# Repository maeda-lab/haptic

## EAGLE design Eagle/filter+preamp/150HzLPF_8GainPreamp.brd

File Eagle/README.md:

Eagle 9.4.1 Education Miyamoto2019/6/6

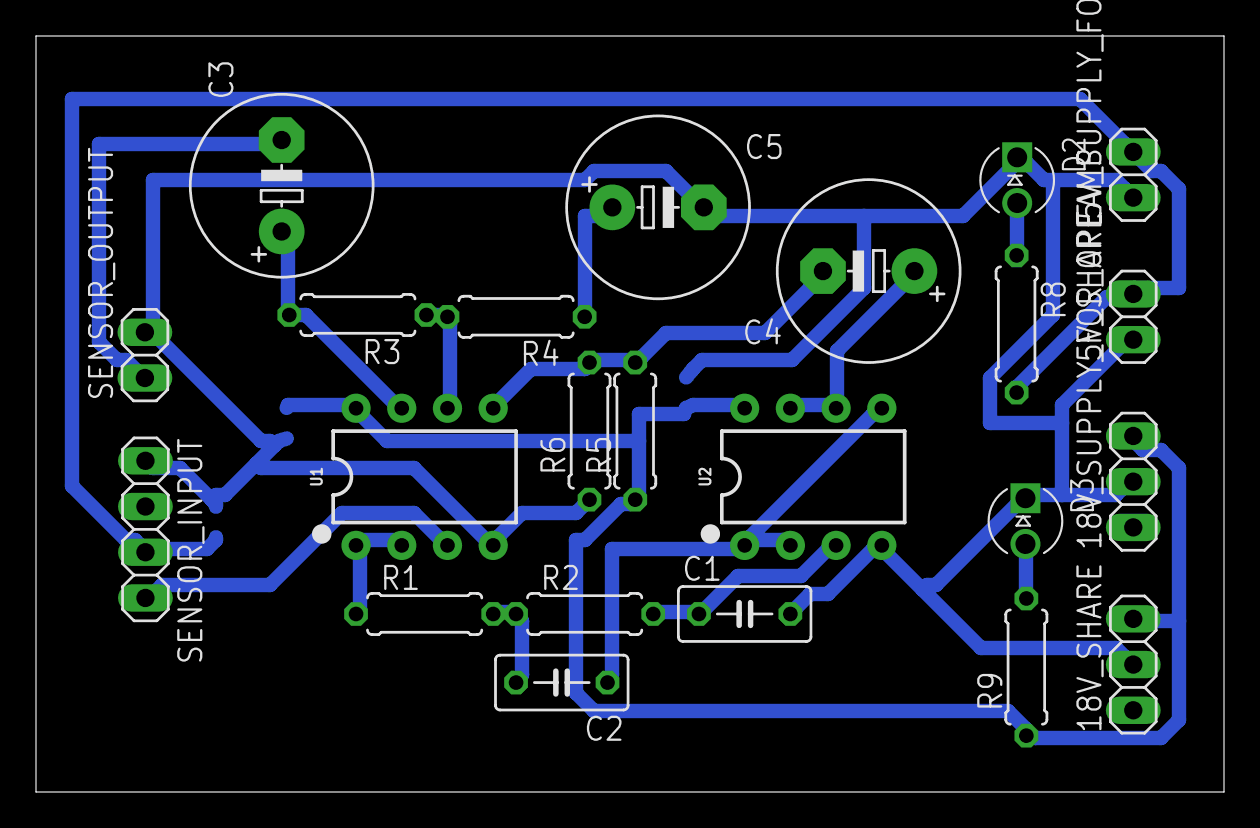
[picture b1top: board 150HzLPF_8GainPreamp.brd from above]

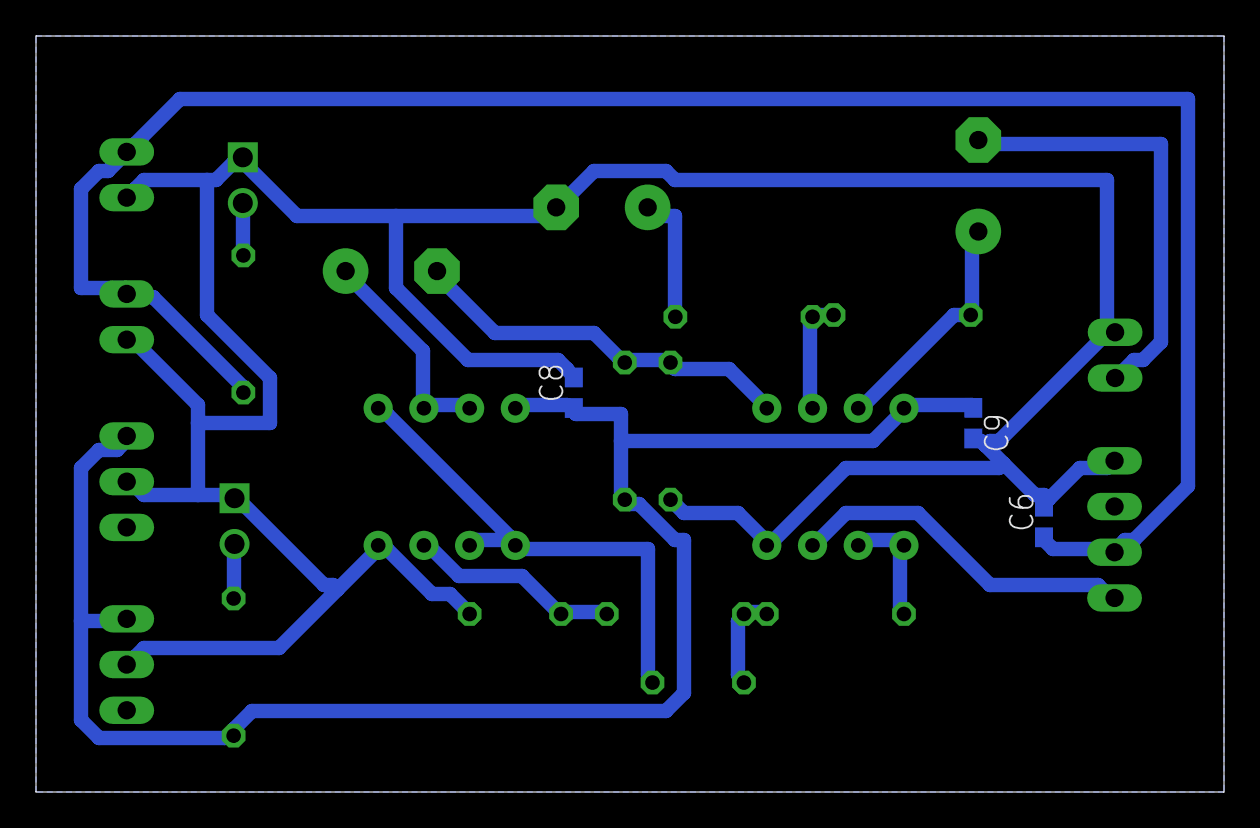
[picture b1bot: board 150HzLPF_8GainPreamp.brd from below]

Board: 2 copper layers, 66.0 x 42.0 mm, 26 parts (3 on the bottom side), 16 nets.

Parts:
5V_SHARE, 5V_SUPPLY_FOR_SENSOR: 1X02
18V_SHARE, 18V_SUPPLY_FOR_OPEAMP: 1X03
C1, C2: 0.1u; C050-030X075
C3: 150u; E5-10,5
C4, C5: 1u or 2.2u; E5-10,5
C6: 0.1u; C0603
C8, C9: 33u; C0603
D2, D3: LTL-1CHE; RADIAL_3MM
R1, R2, R4, R5, R6: 10k; 0207/7
R3: 180k; 0207/7
R8: 760; 0207/7
R9: 3.3k; 0207/7
SENSOR_INPUT: 1X04
SENSOR_OUTPUT: 1X02
U1, U2: LM358; DIP08

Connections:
5V_VCC: 5V_SHARE.2, 5V_SUPPLY_FOR_SENSOR.2, C6.1, R8.2, SENSOR_INPUT.3
18V_VCC: 18V_SHARE.3, 18V_SUPPLY_FOR_OPEAMP.3, C8.1, C9.1, R5.1, R9.1, U1.8, U2.8
GND: 5V_SHARE.1, 5V_SUPPLY_FOR_SENSOR.1, 18V_SHARE.2, 18V_SUPPLY_FOR_OPEAMP.2, C1.2, C5.-, C6.2, C8.2, C9.2, D2.C, D3.C, R6.1, SENSOR_INPUT.1, SENSOR_OUTPUT.2, U1.4, U2.4
unnamed: R1.1, U1.1, U1.2
unnamed: C2.2, R1.2, R2.1
unnamed: C1.1, R2.2, U2.3
unnamed: C2.1, U2.1, U2.2, U2.5
unnamed: SENSOR_INPUT.4, U1.3
unnamed: C4.+, U2.6, U2.7
unnamed: R3.1, R4.2, U1.6
unnamed: C3.+, R3.2, U1.7
unnamed: C4.-, R5.2, R6.2, U1.5
unnamed: C5.+, R4.1
unnamed: D2.A, R8.1
unnamed: C3.-, SENSOR_OUTPUT.1
unnamed: D3.A, R9.2

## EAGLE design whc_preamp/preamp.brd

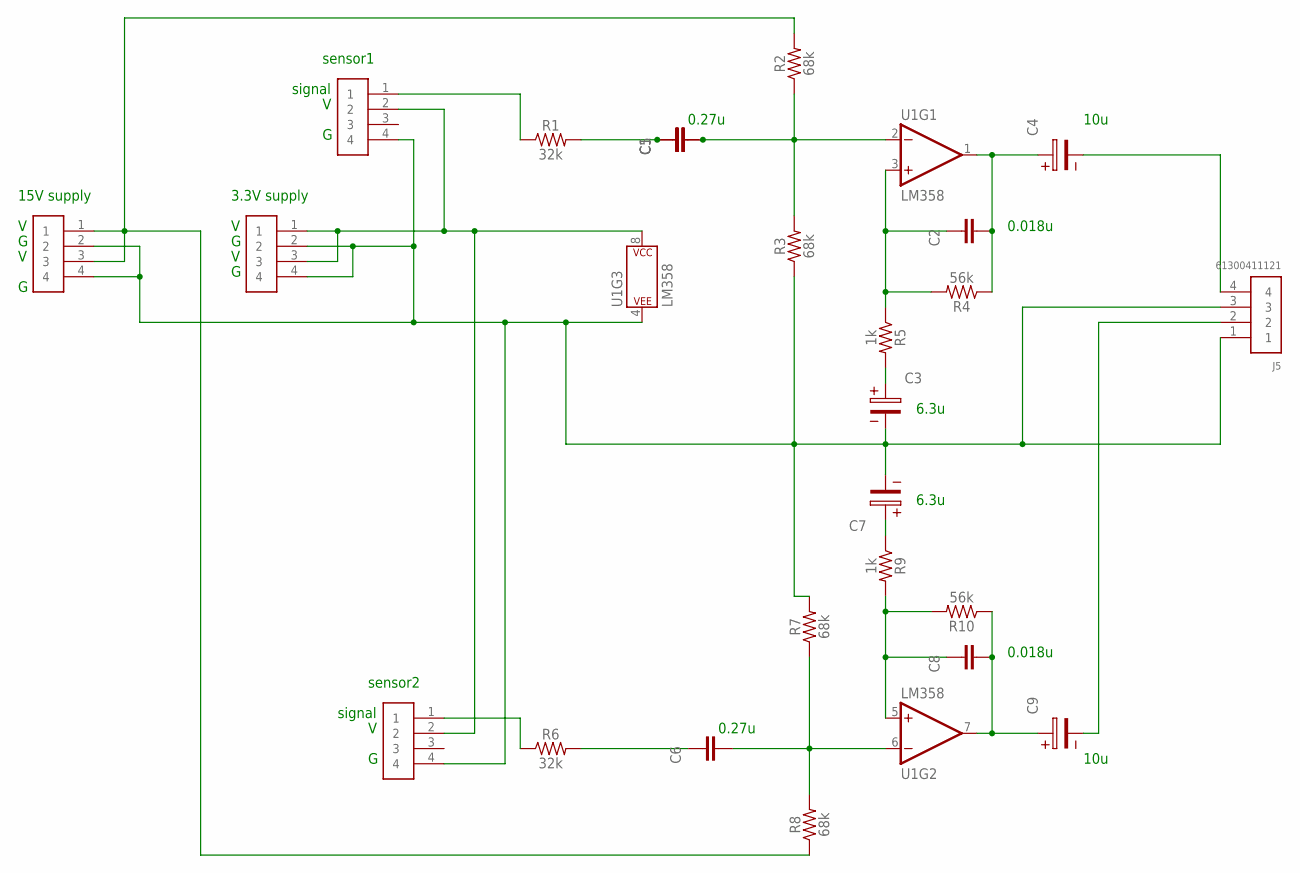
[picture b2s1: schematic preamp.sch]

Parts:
C1, C6, C8: CC0603JRNPO9BN270; CAP_0603
C2: 0.018u; CAP_0603
C3, C4, C7, C9: WCAP-AI3H_25X30_861141084008; 25X10X2(DXPXΦ)
C5: 0.27u; CAP_0603
J1, J2, J3, J4, J5: 61300411121
R1, R6: 32k; AXIAL-0.3
R2, R3, R7, R8: 68k; AXIAL-0.3
R4, R10: 56k; AXIAL-0.3
R5, R9: 1k; AXIAL-0.3
U1: LM358; DIP08

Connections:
unnamed: C1.1, C5.1, R1.P$2 (2)
unnamed: C1.2, C5.2, R2.P$1 (1), R3.P$2 (2), U1.2 (-IN)
unnamed: C2.1, R4.P$2 (2), R5.P$1 (1), U1.3 (+IN)
unnamed: C6.1, R6.P$2 (2)
unnamed: C2.2, C4.1, R4.P$1 (1), U1.1 (OUT)
unnamed: C3.1, R5.P$2 (2)
unnamed: C6.2, R7.P$1 (1), R8.P$2 (2), U1.6 (-IN)
unnamed: C8.1, R9.P$2 (2), R10.P$2 (2), U1.5 (+IN)
unnamed: C8.2, C9.1, R10.P$1 (1), U1.7 (OUT)
unnamed: C7.1, R9.P$1 (1)
unnamed: J1.1, J1.3, J2.2, J3.2, U1.8 (P$V+)
unnamed: J3.1, R1.P$1 (1)
unnamed: J2.1, R6.P$1 (1)
unnamed: C3.2, C7.2, J1.2, J1.4, J2.4, J3.4, J4.2, J4.4, J5.1, J5.3, R3.P$1 (1), R7.P$2 (2), U1.4 (P$V-)
unnamed: C4.2, J5.4
unnamed: C9.2, J5.2
unnamed: J4.1, J4.3, R2.P$2 (2), R8.P$1 (1)

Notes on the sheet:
sensor1
sensor2
3.3V supply
15V supply
signal
0.018u
10u
6.3u
0.27u

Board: 2 copper layers, 25 parts (0 on the bottom side), 17 nets, no tracks yet.

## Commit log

2019-06-06 made folder
2019-06-06 eagle file
2019-06-06 added folder
2019-06-06 wave speed
    wave speed files updated
2019-06-06 added Thesis folder
2019-06-06 preamp -> Eagle
2019-06-06 updated
    updated
2019-06-06 changed
2019-06-06 add poweramp datasheet
2019-06-06 delete
2019-06-06 根原修論
    修論アップデート
2019-06-06 moved pdf
2019-06-06 add tranducer datasheet
2019-06-06 eagle更新
2019-06-11 readme updated
2019-06-13 new eagledata
    VoltageFollower-150LPF-VoltageFollower-preamp
2019-06-17 board file
2019-06-17 final ver.
2019-06-18 Beta GND
2019-06-18 add LED
2019-06-18 consistent error
2019-06-18 add betaGND LED
2019-06-19 add passcon
2019-06-20 Update 150HzLPF_8GainPreamp.b#1
2019-06-21 print board data
2019-06-22 CADdata
2019-06-23 minor change
2019-06-24 3D printer .mpj data
2019-06-30 device cad data
2019-07-04 ファイル整理

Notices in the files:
parts and their libraries:
SparkFun-IC-Amplifiers: Licensing: Creative Commons ShareAlike 4.0 International - https://creativecommons.org/licenses/by-sa/4.0
Wurth_Elektronik_Passive_Capacitors_rev1: Copyright: Würth Elektronik
